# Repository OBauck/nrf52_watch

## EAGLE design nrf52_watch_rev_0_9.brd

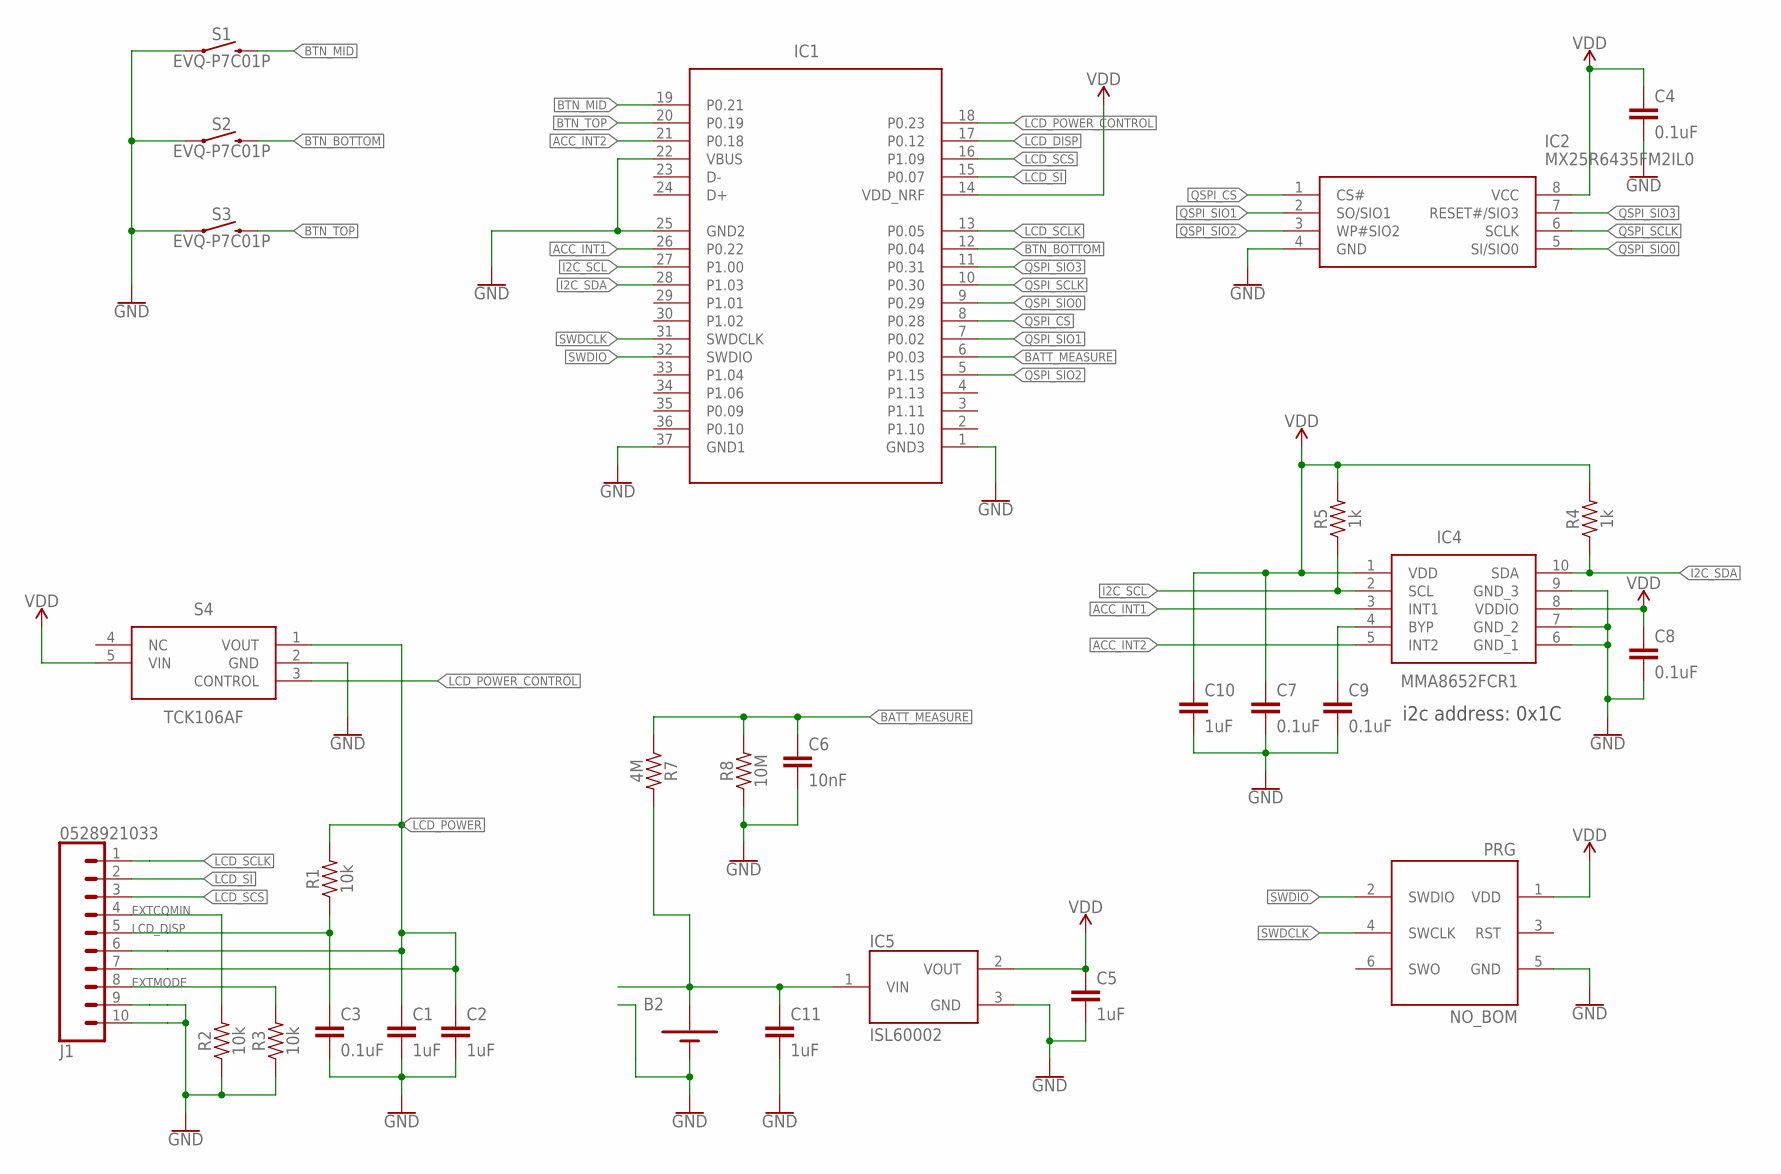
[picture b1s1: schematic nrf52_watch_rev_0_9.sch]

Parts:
B2: BATTERY-BK-916; BK-916-TR
C1, C2, C5, C10, C11: 1uF; C0402
C3, C4, C7, C8, C9: 0.1uF; C0402
C6: 10nF; C0402
IC1: HOLYIOT_18010; HOLYIOT_18010_REDUCED
IC2: MX25R6435FM2IL0; SOIC127P790X216-8N
IC4: MMA8652FCR1; SON40P200X200X100-10N
IC5: ISL60002; SOT23-3
J1: 0528921033
PRG: NO_BOM; 1X06_1.27MM
R1, R2, R3: 10k; R0402
R4, R5: 1k; R0402
R7: 4M; R0402
R8: 10M; R0402
S1, S2, S3: EVQ-P7C01P; EVQP7C01P
S4: TCK106AF; SOT-25

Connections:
ACC_INT1: IC1.26 (P0.22), IC4.3 (INT1)
ACC_INT2: IC1.21 (P0.18), IC4.5 (INT2)
BATT_MEASURE: C6.1, IC1.6 (P0.03), R7.1, R8.2
BTN_BOTTOM: IC1.12 (P0.04), S2.1 (2), S2.4 (2)
BTN_MID: IC1.19 (P0.21), S1.1 (2), S1.4 (2)
BTN_TOP: IC1.20 (P0.19), S3.1 (2), S3.4 (2)
EXTCOMIN: J1.4, R2.2
EXTMODE: J1.8, R3.2
GND: B2.N (-), C1.2, C2.2, C3.2, C4.2, C5.2, C6.2, C7.2, C8.2, C9.2, C10.2, C11.2, IC1.1 (GND3), IC1.22 (VBUS), IC1.25 (GND2), IC1.37 (GND1), IC2.4 (GND), IC4.6 (GND_1), IC4.7 (GND_2), IC4.9 (GND_3), IC5.3 (GND), J1.9, J1.10, PRG.5 (GND), R2.1, R3.1, R8.1, S1.2 (1), S1.3 (1), S2.2 (1), S2.3 (1), S3.2 (1), S3.3 (1), S4.2 (GND)
I2C_SCL: IC1.27 (P1.00), IC4.2 (SCL), R5.1
I2C_SDA: IC1.28 (P1.03), IC4.10 (SDA), R4.1
LCD_DISP: C3.1, IC1.17 (P0.12), J1.5, R1.1
LCD_POWER: C1.1, C2.1, J1.6, J1.7, R1.2, S4.1 (VOUT)
LCD_POWER_CONTROL: IC1.18 (P0.23), S4.3 (CONTROL)
LCD_SCLK: IC1.13 (P0.05), J1.1
LCD_SCS: IC1.16 (P1.09), J1.3
LCD_SI: IC1.15 (P0.07), J1.2
unnamed: B2.P1 (+), B2.P2 (+), C11.1, IC5.1 (VIN), R7.2
unnamed: C9.1, IC4.4 (BYP)
QSPI_CS: IC1.8 (P0.28), IC2.1 (CS#)
QSPI_SCLK: IC1.10 (P0.30), IC2.6 (SCLK)
QSPI_SIO0: IC1.9 (P0.29), IC2.5 (SI/SIO0)
QSPI_SIO1: IC1.7 (P0.02), IC2.2 (SO/SIO1)
QSPI_SIO2: IC1.5 (P1.15), IC2.3 (WP#SIO2)
QSPI_SIO3: IC1.11 (P0.31), IC2.7 (RESET#/SIO3)
SWDCLK: IC1.31 (SWDCLK), PRG.4 (SWCLK)
SWDIO: IC1.32 (SWDIO), PRG.2 (SWDIO)
VDD: C4.1, C5.1, C7.1, C8.1, C10.1, IC1.14 (VDD_NRF), IC2.8 (VCC), IC4.1 (VDD), IC4.8 (VDDIO), IC5.2 (VOUT), PRG.1 (VDD), R4.2, R5.2, S4.5 (VIN)

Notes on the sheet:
i2c address: 0x1C

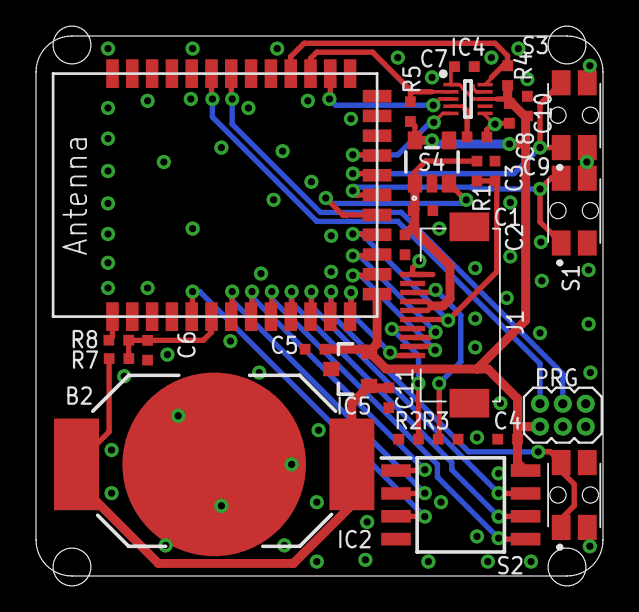
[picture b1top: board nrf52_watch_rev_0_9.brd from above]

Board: 2 copper layers, 31.5 x 30.0 mm, 29 parts (0 on the bottom side), 28 nets.

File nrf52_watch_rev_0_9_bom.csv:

"Design title:";"nrf52_watch_rev_0_9"
"Date:";"03.11.2018 12.11"
"Designer:";"Ole Bauck"
"Company:";"Inventas"

"Item";"Qty";"Refdes";"Description";"Value";"MANUFACTURER_PART_NUMBER";"MANUFACTURER_NAME";
"1";"5";"C3, C4, C7, C8, C9";"CAP-6.3V-20%-0402";"0.1uF";"";"";
"2";"1";"J1";"0528921033";"0528921033";"0528921033";"Molex";
"3";"1";"R8";"RES-0.063W-1%-0402";"10M";"";"";
"4";"3";"R1, R2, R3";"RES-0.063W-5%-0402";"10k";"";"";
"5";"1";"C6";"CAP-6.3V-20%-0402";"10nF";"";"";
"6";"2";"R4, R5";"RES-0.063W-5%-0402";"1k";"";"";
"7";"5";"C1, C2, C5, C10, C11";"CAP-6.3V-20%-0402";"1uF";"";"";
"8";"1";"R7";"RES-0.063W-1%-0402";"4M";"";"";
"9";"1";"B2";"BATTERY-BK-916";"BATTERY-BK-916";"BK-916-TR";"MPD";
"10";"3";"S1, S2, S3";"EVQ-P7C01P";"EVQ-P7C01P";"EVQ-P7C01P";"Panasonic";
"11";"1";"IC1";"HOLYIOT_18010";"HOLYIOT_18010";"18010";"Holyiot";
"12";"1";"IC5";"ISL60002";"ISL60002";"";"";
"13";"1";"IC4";"MMA8652FCR1";"MMA8652FCR1";"MMA8652FCR1";"NXP";
"14";"1";"IC2";"MX25R6435FM2IL0";"MX25R6435FM2IL0";"MX25R6435FM2IL0";"Macronix";
"15";"1";"S4";"TCK106AF";"TCK106AF";"TCK106AF";"Toshiba";

"The following components shall not be mounted"
"Item";"Qty";"Refdes";"Description";"Value";"MANUFACTURER_PART_NUMBER";"MANUFACTURER_NAME";

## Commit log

2018-10-12 first commit. most components placed
2018-10-12 first draft of routing done
2018-10-13 added zip
2018-10-13 changes to rouing. Added batter voltage measure. Added mounting holes
2018-10-13 addded 3D files
2018-10-13 small fixes. all components are now 3D

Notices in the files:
parts and their libraries:
SparkFun-Aesthetics: Licensing: Creative Commons ShareAlike 4.0 International - https://creativecommons.org/licenses/by-sa/4.0
